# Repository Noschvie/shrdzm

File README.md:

## SHRDZM is intended to become an end-to-end integration platform.
It provides wiring digrams, source code and working examples.
Also plug-ins for most commonly used home automation solutions will be collected.

To build cheap integrations of many kind of sensors and/or actors into your own automation solution with the focus on energy efficiancy (battery operated devices) and simpleness.

Take a look on the [Wiki](https://github.com/saghonfly/shrdzm/wiki)

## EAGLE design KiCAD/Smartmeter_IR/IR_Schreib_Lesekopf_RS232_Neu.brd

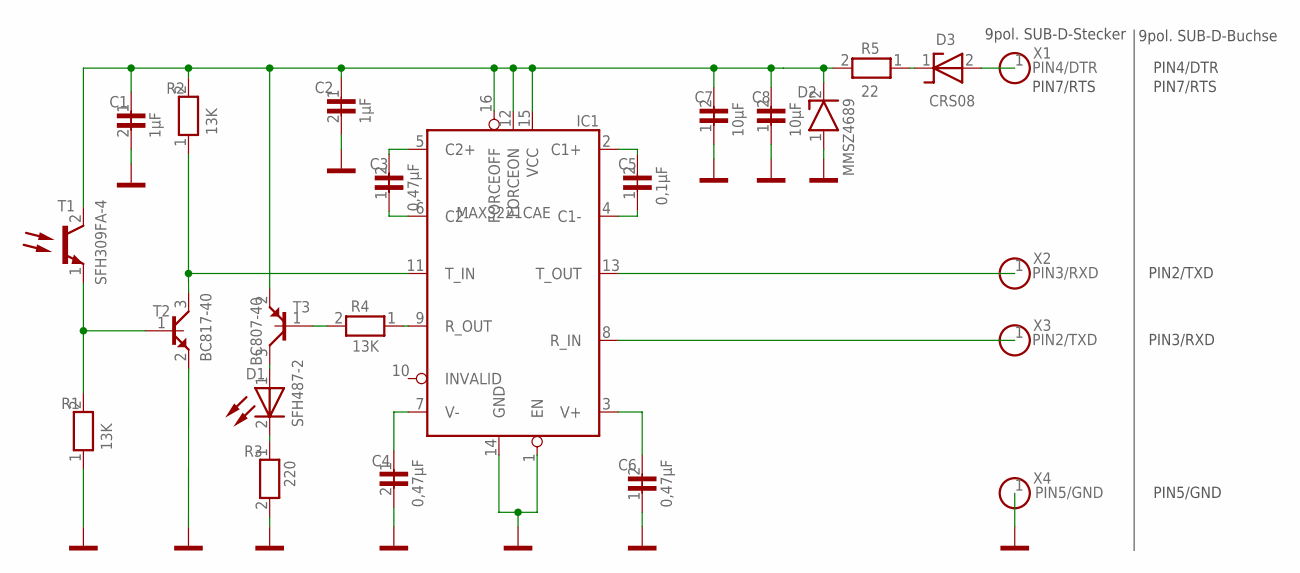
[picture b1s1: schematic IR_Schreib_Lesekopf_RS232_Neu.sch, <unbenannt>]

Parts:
C1: 1µF; 0603_KLEIN_25
C2: 1µF; 1206_29
C3: 0,47µF; 0603_13
C4: 0,47µF; 0603_0
C5: 0,1µF; 0603_12
C6: 0,47µF; 0603_1
C7: 10µF; 0805_KLEIN_34
C8: 10µF; 0805_KLEIN_2
D1: SFH487-2; LED_3MM_26
D2: MMSZ4689; DO214AA_15
D3: CRS08; SOD123_17
IC1: MAX3221CAE; SSOP16_11
R1: 13K; 0603_KLEIN_20
R2: 13K; 0603_KLEIN_21
R3: 220; 0603_KLEIN_31
R4: 13K; 0603_KLEIN_27
R5: 22; 1206_18
T1: SFH309FA-4; FOTO_4MM_19
T2: BC817-40; SOT23/3_33
T3: BC807-40; SOT23/3_32
X1: PIN4/DTR; LOETPUNKT_7
X2: PIN3/RXD; LOETPUNKT_9
X3: PIN2/TXD; LOETPUNKT_8
X4: PIN5/GND; LOETPUNKT_10

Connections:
2: D3.1, R5.1
+: R1.2, T1.1, T2.1
B: R4.2, T3.1
C: D1.1, T3.3
C1+: C5.2, IC1.2 (C1+)
C1-: C5.1, IC1.4 (C1-)
C2+: C3.2, IC1.5 (C2+)
C2-: C3.1, IC1.6 (C2-)
GND: C1.2, C2.2, C4.2, C6.1, C7.1, C8.1, D2.1, IC1.1 (EN), IC1.14 (GND), R1.1, R3.2, T2.2, X4.1
K: D1.2, R3.1
PIN1: D3.2, X1.1
RXD: IC1.11 (T_IN), R2.1, T2.3
R_OUT: IC1.9 (R_OUT), R4.1
SIG$10: IC1.13 (T_OUT), X2.1
SIG$11: IC1.8 (R_IN), X3.1
V+: C6.2, IC1.3 (V+)
V-: C4.1, IC1.7 (V-)
VCC: C1.1, C2.1, C7.2, C8.2, D2.2, IC1.12 (FORCEON), IC1.15 (VCC), IC1.16 (FORCEOFF), R2.2, R5.2, T1.2, T3.2

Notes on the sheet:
9pol. SUB-D-Stecker
PIN7/RTS
PIN4/DTR
PIN2/TXD
PIN3/RXD
PIN5/GND
9pol. SUB-D-Buchse

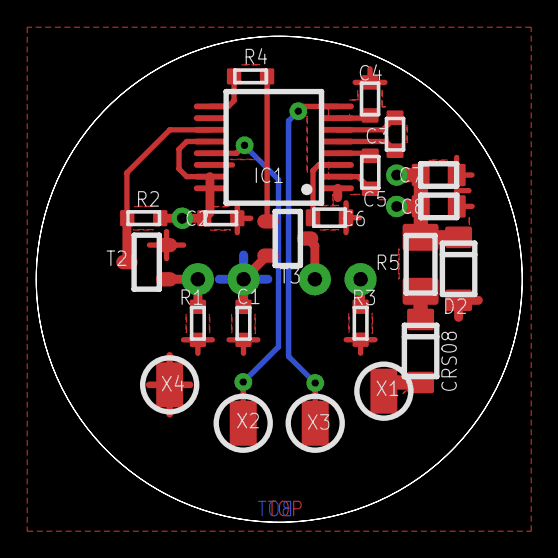
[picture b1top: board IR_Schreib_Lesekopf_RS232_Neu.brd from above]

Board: 2 copper layers, 27.0 x 27.0 mm, 24 parts (1 on the bottom side), 18 nets.

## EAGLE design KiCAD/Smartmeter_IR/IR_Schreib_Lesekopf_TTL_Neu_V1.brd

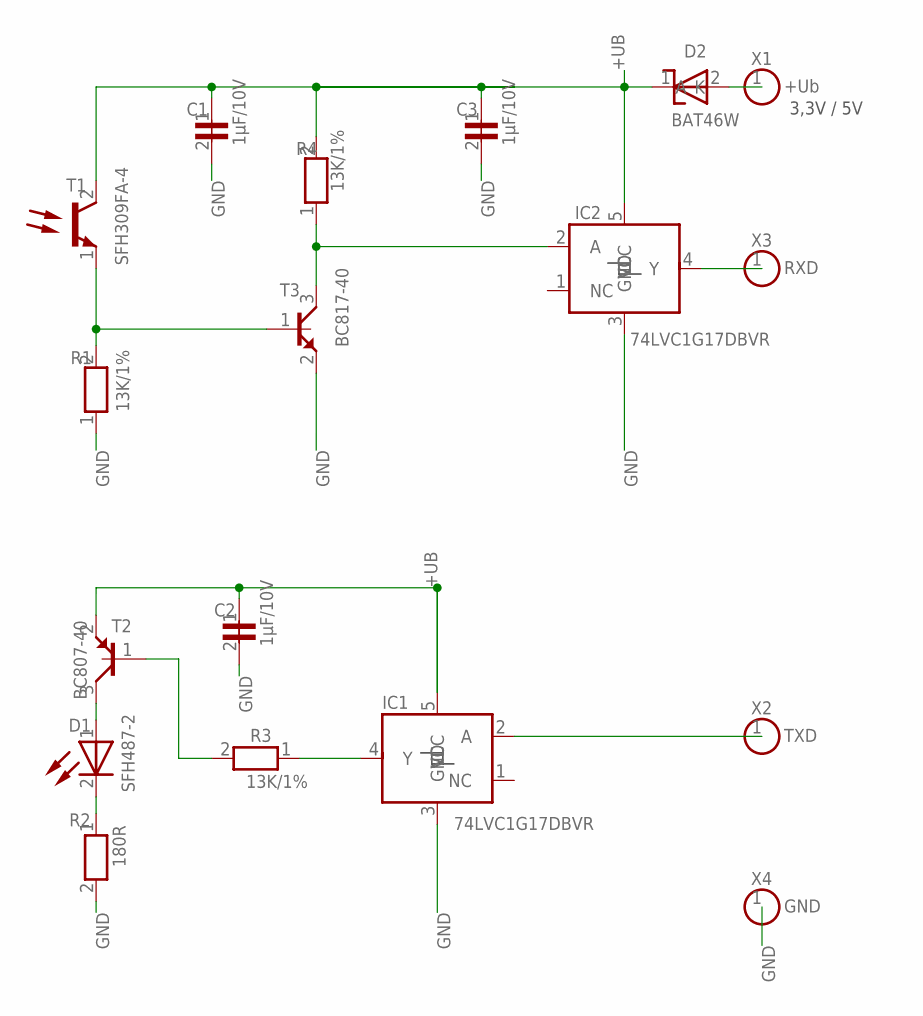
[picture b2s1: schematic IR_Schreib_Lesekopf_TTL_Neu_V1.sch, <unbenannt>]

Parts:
C1: 1µF/10V; 0805_11
C2: 1µF/10V; 0805_21
C3: 1µF/10V; 0805_10
D1: SFH487-2; LED_3MM_13
D2: BAT46W; SOD123_25
IC1: 74LVC1G17DBVR; SOT23/5_20
IC2: 74LVC1G17DBVR; SOT23/5_23
R1: 13K/1%; 0805_5
R2: 180R; 0805_27
R3: 13K/1%; 0805_14
R4: 13K/1%; 0805_6
T1: SFH309FA-4; FOTO_4MM_4
T2: BC807-40; SOT23/3_28
T3: BC817-40; SOT23/3_26
X1: +Ub; LOETPUNKT_3
X2: TXD; LOETPUNKT_19
X3: RXD; LOETPUNKT_2
X4: GND; LOETPUNKT_1

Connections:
1: IC1.4 (Y), R3.1
+: R1.2, T1.1, T3.1
+UB: C1.1, C2.1, C3.1, D2.1 (K), IC1.5 (VCC), IC2.5 (VCC), R4.2, T1.2, T2.2
A: D2.2 (A), X1.1
B: R3.2, T2.1
C: D1.1, T2.3
GND: C1.2, C2.2, C3.2, IC1.3 (GND), IC2.3 (GND), R1.1, R2.2, T3.2, X4.1
K: D1.2, R2.1
OUT: IC2.2 (A), R4.1, T3.3
SIG$4: IC1.2 (A), X2.1
SIG$5: IC2.4 (Y), X3.1

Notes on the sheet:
3,3V / 5V

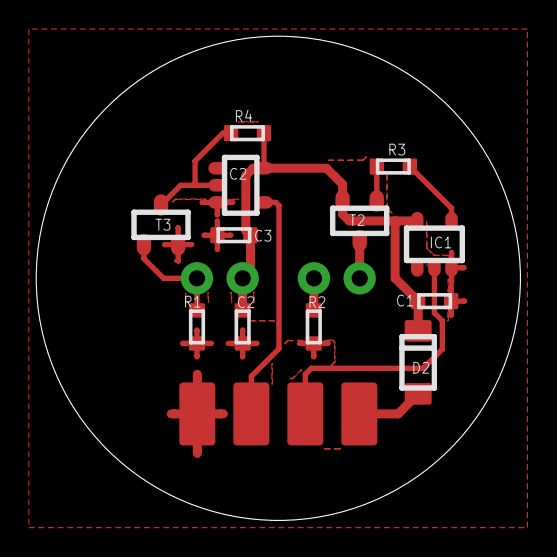
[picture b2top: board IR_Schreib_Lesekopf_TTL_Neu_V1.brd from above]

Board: 2 copper layers, 26.9 x 26.9 mm, 18 parts (1 on the bottom side), 11 nets.

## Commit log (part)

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2020-08-29 OTA for serial added
2020-10-20 IM350 added
2020-10-26 IM350 max read time changed
2020-11-06 IM350 updated
2020-12-07 Update Logo
2020-12-14 Update IM350 to inbuild decoding
2021-01-09 First version of 4th generation
2021-01-10 Back to 0.3.3
2021-01-16 Upgrade
2021-01-16 Upgrade to Version 0.4.0
2021-01-18 Auto Pairing added
2021-01-24 IM350 Picture Upload
2021-01-24 OTA for SHRDZMDevice added in Gateway Mode
2021-02-05 Dewpoint added for HTU21 sensor
2021-02-05 Heat Index added for DHT22 and HTU21
2021-02-06 SDS011_BH1750 added
2021-02-11 Water BOM added
2021-02-20 Update Wiring
2021-02-27 Doorsensor added
2021-03-04 IM350 Bugfix
2021-03-07 IM350 Correction
    IM350 was always showing same values in permanent online mode (Integration Style ZERO) due to uninitialited cipher object.
2021-03-20 KiCAD files added
2021-03-21 Doorsensor PCB added
2021-03-21 DOORSENSOR Updated
2021-03-23 SDS011 Circuit added
2021-03-25 DOORSENSOR state error added
2021-03-25 DOORSENSOR upgraded
2021-04-03 AM550 Smartmeter added
2021-04-04 IM350 SoftwareSerial added
2021-04-04 IM350 Invert Serial added
2021-04-07 IM350_AM550_5V Gerber files added
2021-04-10 Update 3D Models
2021-04-12 Bootreason added
2021-04-15 DOORSENSOR 9V KiCAD added
2021-05-05 Website last measurement values added
2021-05-23 IM350 Wels added
2021-05-24 IM350 Wels bug fix
2021-05-30 Experimental Cloud added
2021-05-31 Cloud REST added
2021-05-31 Cloud files added
2021-06-01 Cloud functions
2021-06-03 Refresh Cloud Token added
2021-06-03 Update Alexa Authentification
2021-06-03 Update Alexa
2021-06-04 Update Alexa Token Handling
2021-06-04 Logo update
2021-06-05 Update Alexa APi
2021-06-07 MQTTGateway SoftwareSerial fixed
2021-06-08 OTA Upgrade via Web Explorer
2021-07-04 Publish Checksum Error
2021-07-05 Cloud Server Files Update
2021-07-18 Changed Smartmeter to Crypto lib usage
2021-08-01 SmartMeter update
2021-08-01 Website update
2021-08-03 IM350 hourWatt added
2021-08-05 SmartMeter Statistic added
2021-08-08 Website handleSettings bugfix
2021-08-12 IM350 Cloud Update bugfix
2021-08-14 Smartmeter Description Updated
2021-08-15 SHRDZMGatewayMQTT Updated
2021-08-17 Update SHRDZMGatewayMQTT
2021-08-20 IM350 removed invalid values
2021-08-21 MQTT Connection set to optional
2021-10-06 Smartmeter Energie Steiermark added
2021-10-09 JSon send format added
2021-10-17 Smartmeter updated
2021-10-22 Private Cloud data send added to SHRDZMDevice
2021-10-25 Smartmeter IR Head added
2021-11-20 AM550 Smartmeter from Slovenia added
2021-11-21 Smartmeter AM550 end byte detection added
2021-11-23 Update AM550 Slovenia
2021-11-23 Base for Version 0.5.2
2022-01-01 MBus for Smartmeter added
2022-01-02 KiCAD update
2022-01-05 Smartmeter Vienna E450 added
2022-01-10 Smartmeter TINETZ added
2022-01-10 Update SHRDZM_www logo
2022-01-17 Added Smartmeter IR Vienna
2022-01-19 Styria Smartmeter enhanced
2022-01-30 Slovenia unencrypted AM550 Smartmeter added
2022-02-03 MQTT Topic corrected
